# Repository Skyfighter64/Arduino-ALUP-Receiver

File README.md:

# Arduino-ALUP-Receiver
This repository contains Ki-CAD design files for the PCB of my Arduino ALUP Receiver hardware.

## Overview
The circuit uses an optocoupler to galvanically isolate the Arduino from the LED hardware.
This should prevent the connected USB-Device from frying if something goes wrong with the LEDs or the LED power supply.

Note that not any optocupler can be used, it has to be fast enough to support the communication speed of your LEDs (800Kbps for WS2812b, Spoiler: PC817s DON'T). 

There is also a 3A fuse included to protect the Power Supply from burning down due to overcurrent.
The number of connected LEDs should be limited so they don't pull more than 3A through the connected power supply.

## Disclaimer
The files provided are without any warranty or liability for any kind of damages. Building the device, following the provided instructions, operation of the device, and everything else is at your own risk. For more see license file.

## Bill Of Materials
Hardware Components needed for assembly:
- Arduino Nano (or clone)
- female pin headers for Arduino (optional but recommended)
- 6N137 Optocoupler
- 220 Ohm resistor
- 470 Ohm resistor
- 3A THT Fuse
- DC barrel jack socket
- DC 5V, >= 3A Power Supply with barrel jack (Negative Outside, Positive Inside), (depends on number of LEDs)
- JST SM 3 Pin LED connector (depends on used LEDs)

## Building instructions
- Solder components to the PCB.
    1. Start with soldering the Optocoupler. The correct orientation is marked on the PCB.
    2. Continue with resistors and power jack socket according to the prints on the PCB.
    3. Solder the fuse
    4. Solder the JST connector. Usual wiring is 5V:Red, GND: White, D+: Green (May differ depending on LED strips). The cables can be looped through the three marked holes for some pull-protection.
    5. Solder the arduino (or female pin headers) to the PCB in the marked orientation.  

## Software
To install Arduino-ALUP, see [here](https://github.com/Skyfighter64/Arduino-ALUP)
Note: The LEDs are connected to GPIO 2 of the Arduino Board.

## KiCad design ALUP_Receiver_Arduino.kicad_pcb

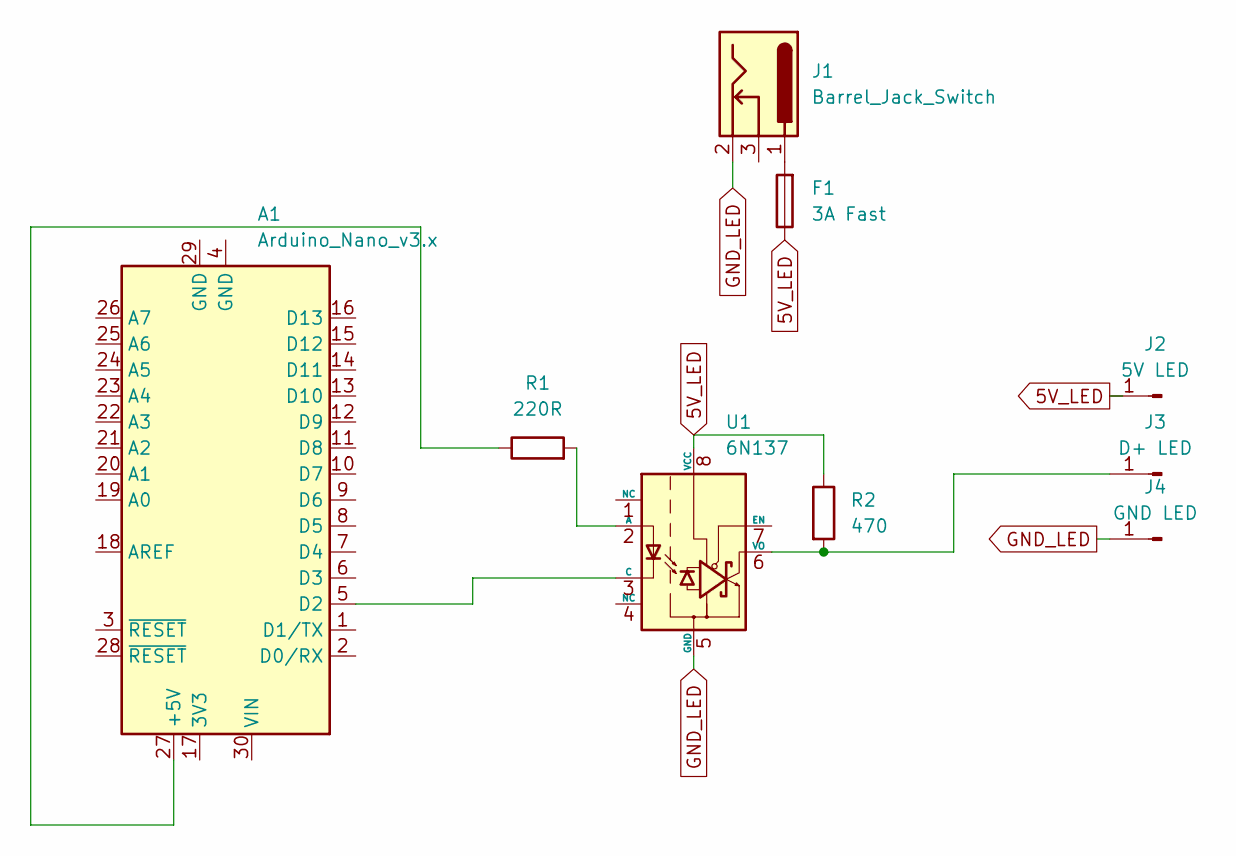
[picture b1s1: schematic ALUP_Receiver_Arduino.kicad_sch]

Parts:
A1: Arduino_Nano_v3.x; Arduino_Nano
F1: 3A Fast; R_Axial_DIN0411_L9.9mm_D3.6mm_P15.24mm_Horizontal
J1: Barrel_Jack_Switch; BarrelJack_Kycon_KLDX-0202-xC_Horizontal
J2: 5V LED; SolderWire-0.5sqmm_1x01_D0.9mm_OD2.1mm_Relief
J3: D+ LED; SolderWire-0.5sqmm_1x01_D0.9mm_OD2.1mm_Relief
J4: GND LED; SolderWire-0.5sqmm_1x01_D0.9mm_OD2.1mm_Relief
R1: 220R; R_Axial_DIN0207_L6.3mm_D2.5mm_P10.16mm_Horizontal
R2: 470; R_Axial_DIN0207_L6.3mm_D2.5mm_P10.16mm_Horizontal
U1: 6N137; DIP-8_W7.62mm

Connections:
5V_LED: F1.1, J2.1, R2.1, U1.8 (VCC)
GND_LED: J1.2, J4.1, U1.5 (GND)
unnamed: A1.27 (+5V), R1.1
unnamed: A1.5 (D2), U1.3 (C)
unnamed: F1.2, J1.1
unnamed: J3.1, R2.2, U1.6 (VO)
unnamed: R1.2, U1.2 (A)

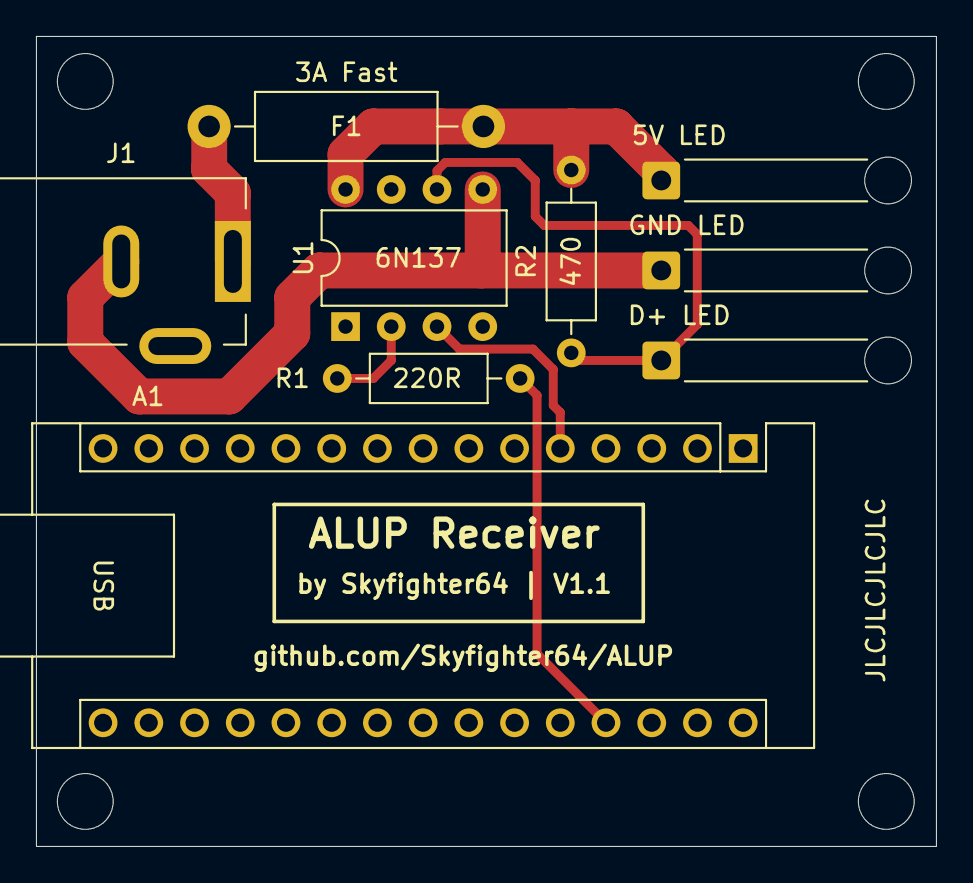
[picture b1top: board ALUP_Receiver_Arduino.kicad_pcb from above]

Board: 2 copper layers, 50.0 x 45.0 mm, 9 parts (0 on the bottom side), 7 nets.

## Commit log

2025-07-17 Change pullup resistor
2025-07-17 Adjust pullup im BOM
